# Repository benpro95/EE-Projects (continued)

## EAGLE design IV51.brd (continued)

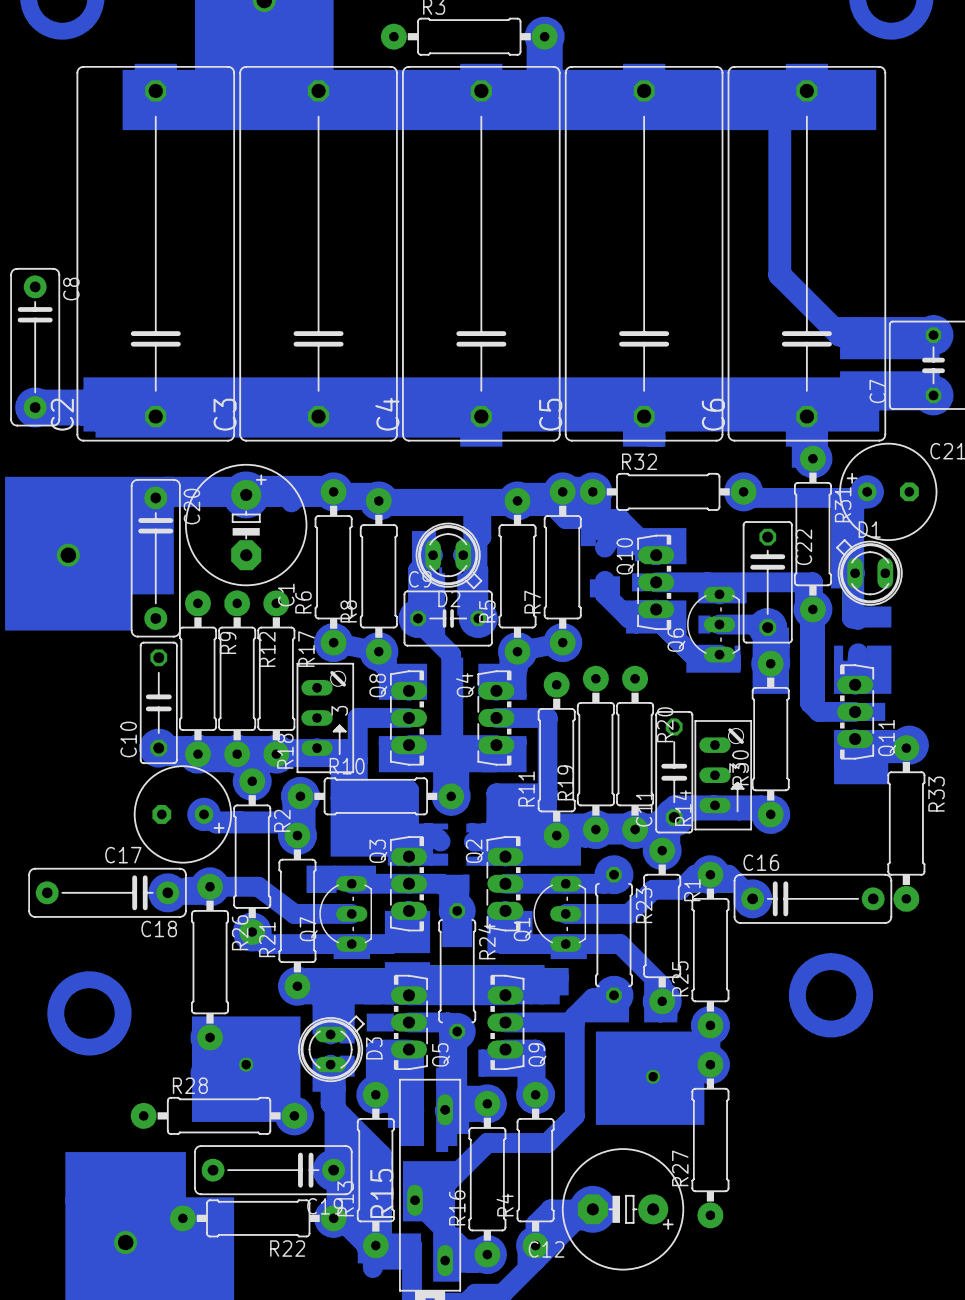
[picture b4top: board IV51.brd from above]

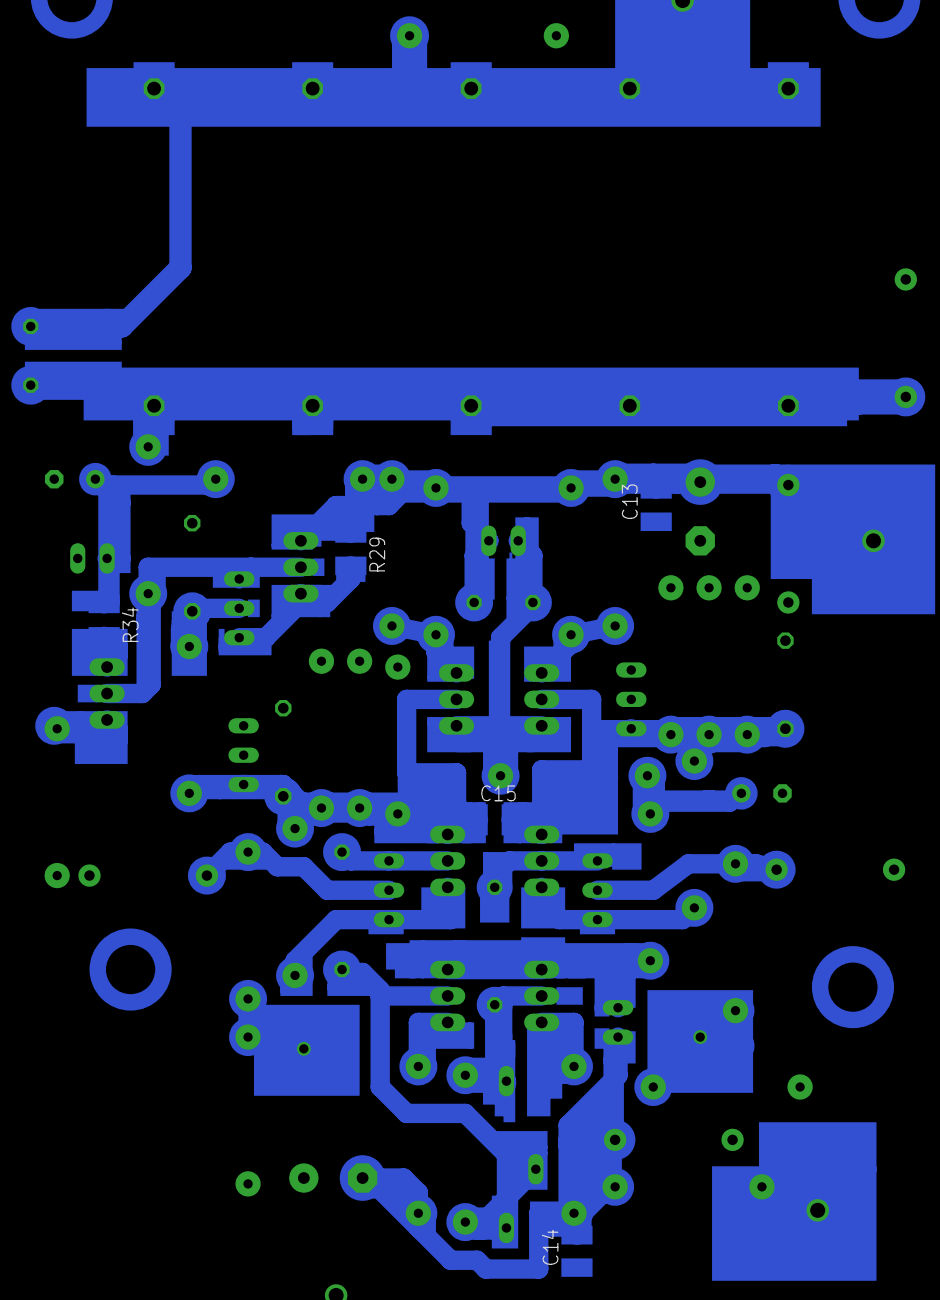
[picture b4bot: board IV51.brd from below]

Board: 2 copper layers, 70 parts (5 on the bottom side), 30 nets.

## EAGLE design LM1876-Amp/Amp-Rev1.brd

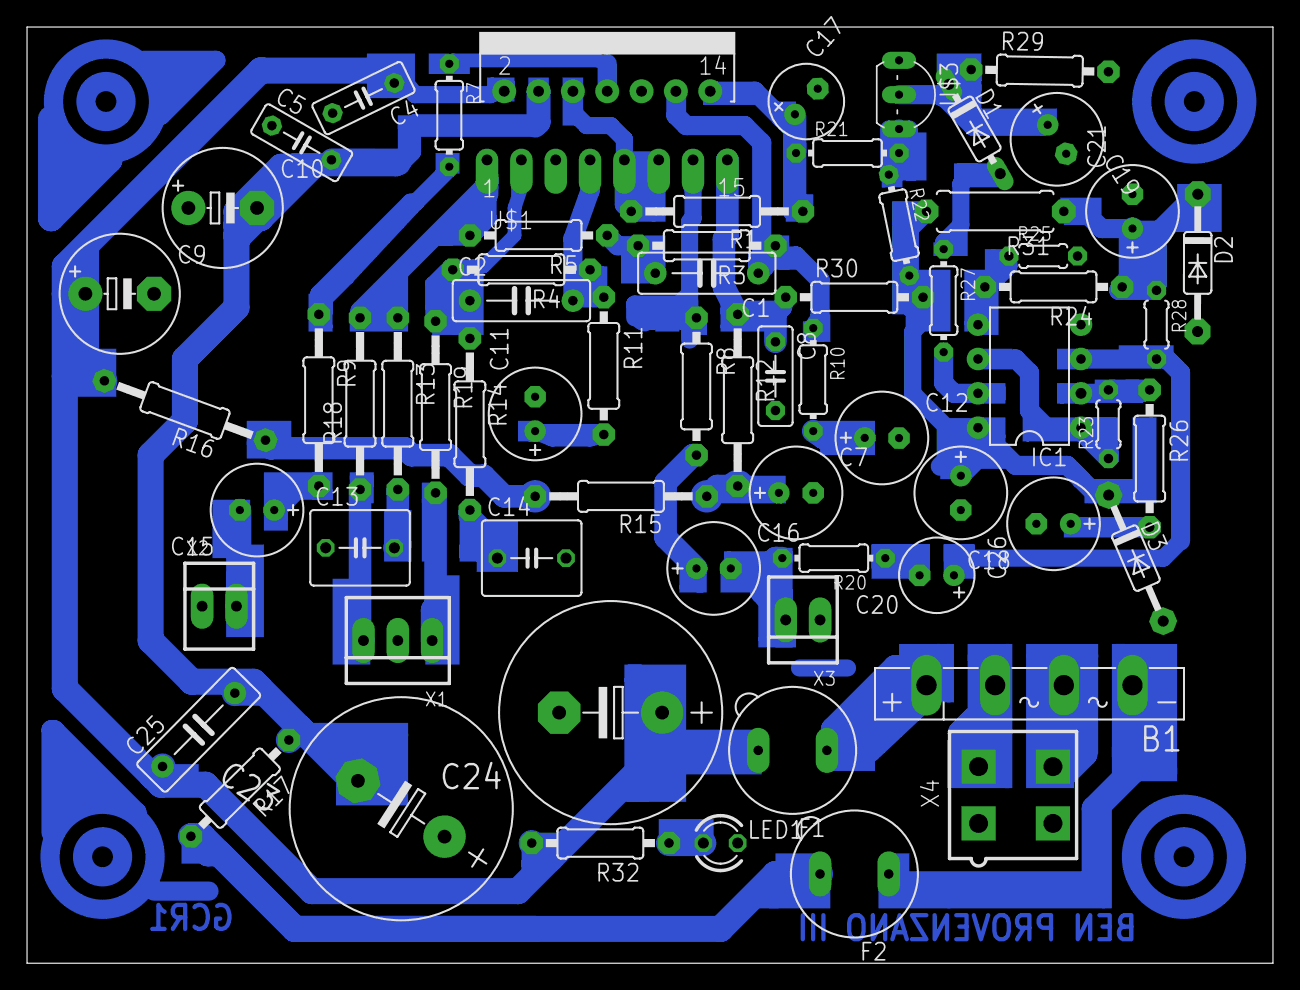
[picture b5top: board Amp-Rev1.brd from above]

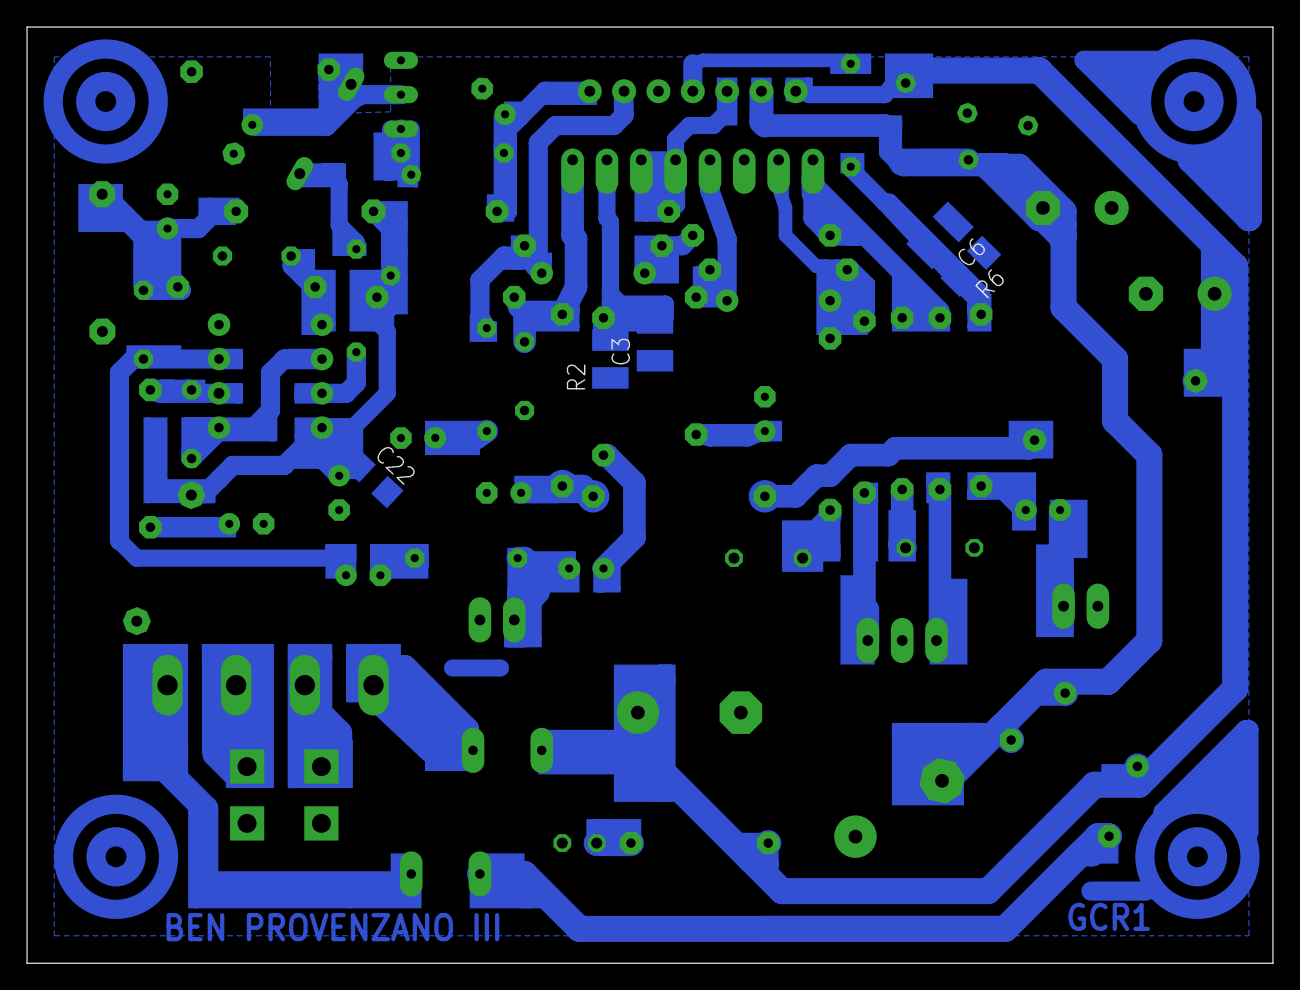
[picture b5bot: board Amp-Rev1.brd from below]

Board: 2 copper layers, 92.2 x 69.3 mm, 72 parts (5 on the bottom side), 44 nets.

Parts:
B1: GBU4S
C1, C2: 22pF; C075-032X103
C3, C6: 220pF; C1210
C4, C5, C8: 0.1; C050-025X075
C7: 10uF; E2,5-7
C9, C10: 220uF; E5-8,5
C11, C12, C18, C19, C21, C26: 47uF; E2,5-7
C13, C14: 0.1 PP; C050-055X075
C15, C16: 22uF BP; E2,5-7
C17: 10uF; E2,5-6
C20: 1uF; E2,5-6
C22: 0.1; C1206
C23, C24: 4700uF; E7,5-16
C25: 0.15; C075-032X103
D1: 4148; DO35-7
D2: 5v1; DO35-10
D3: 12v; DO35-10
F1, F2: 3A; 19560
IC1: LM358N; DIL08
LED1: RED; LED3MM
R1, R12, R15, R16: J; 0207/12
R2: 25k; R1210
R3, R4: 25k; 0207/10
R5, R17: J; 0207/10
R6: 47k; M1206
R7: J; 0204/7
R8, R11, R26: 1k; 0207/10
R9: 1k; 0207/12
R10: 1k; 0204/7
R13, R14: 4.7; 0207/12
R18, R19: 10R+0.7H; 0207/12
R20, R22: 10k; 0204/7
R21: 25k; 0204/7
R23, R25, R28: 100k; 0204/5
R24: 10k; 0207/10
R27: 100; 0204/7
R29: 10M; 0207/10
R30: 820R; 0207/10
R31: 2k2; 0309/10
R32: 3k9; 0207/10
U$1: LM1876; MULTIWATT-15
U$3: 2N7000; TO92-
X1: OUT; 22-23-2031
X2, X3: IN; 22-23-2021
X4: AC; 5566-4

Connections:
GND: C3.1, C4.2, C5.1, C6.1, C7.-, C8.2, C9.-, C10.+, C11.-, C12.-, C13.1, C14.2, C17.-, C18.-, C19.-, C21.-, C22.2, C23.+, C24.-, C26.-, D2.A, D3.A, IC1.4, LED1.K, R2.1, R6.1, R25.2, R29.2, U$1.5, U$1.10, U$3.3, X1.2, X2.1, X3.1, X4.1, X4.3
unnamed: R7.1, U$1.8
unnamed: R1.2, U$1.6, U$1.9, U$1.11
unnamed: C1.2, R3.2, R5.1
unnamed: C6.2, R6.2, R7.2, R9.1
unnamed: C2.2, R4.1, R11.1, U$1.7
unnamed: C5.2, C10.-, C23.-, C25.2, R17.1, U$1.4
unnamed: C2.1, R4.2, R14.1, R19.1, U$1.3
unnamed: C4.1, C9.+, C24.+, C25.1, F1.2, R16.2, R32.2, U$1.2
unnamed: R5.2, R13.1, R18.2, U$1.1
unnamed: C1.1, R3.1, R10.1, U$1.12
unnamed: R15.2, R16.1
unnamed: C22.1, C26.+, D3.C, IC1.8, R22.2, R30.2, R31.2
unnamed: C7.+, R12.2, R15.1
unnamed: C17.+, R1.1, R21.1, U$1.14
unnamed: C12.+, R10.2
unnamed: C11.+, R11.2
unnamed: C3.2, R2.2, R8.1, U$1.13
unnamed: C13.2, R13.2
unnamed: C14.1, R14.2
unnamed: R18.1, X1.3
unnamed: R19.2, X1.1
unnamed: C15.+, R9.2
unnamed: C15.-, X2.2
unnamed: C20.-, R20.1
unnamed: C16.+, R8.2
unnamed: C16.-, R20.2, X3.2
unnamed: LED1.A, R32.1
unnamed: C19.+, D1.C, R29.1, U$3.2
unnamed: IC1.2, R23.2, R26.1
unnamed: IC1.1, IC1.6, R23.1
unnamed: C20.+, IC1.3, R28.2
unnamed: IC1.5, R24.2, R25.1
unnamed: C18.+, R26.2
unnamed: C8.1, R12.1, R30.1, U$1.15
unnamed: IC1.7, R27.2
unnamed: C21.+, D2.C, R24.1, R28.1, R31.1
unnamed: R21.2, R22.1, U$3.1
unnamed: D1.A, R27.1
unnamed: B1.+, F1.1
unnamed: F2.2, R17.2
unnamed: B1.-, F2.1
unnamed: B1.AC1, X4.2
unnamed: B1.AC2, X4.4
